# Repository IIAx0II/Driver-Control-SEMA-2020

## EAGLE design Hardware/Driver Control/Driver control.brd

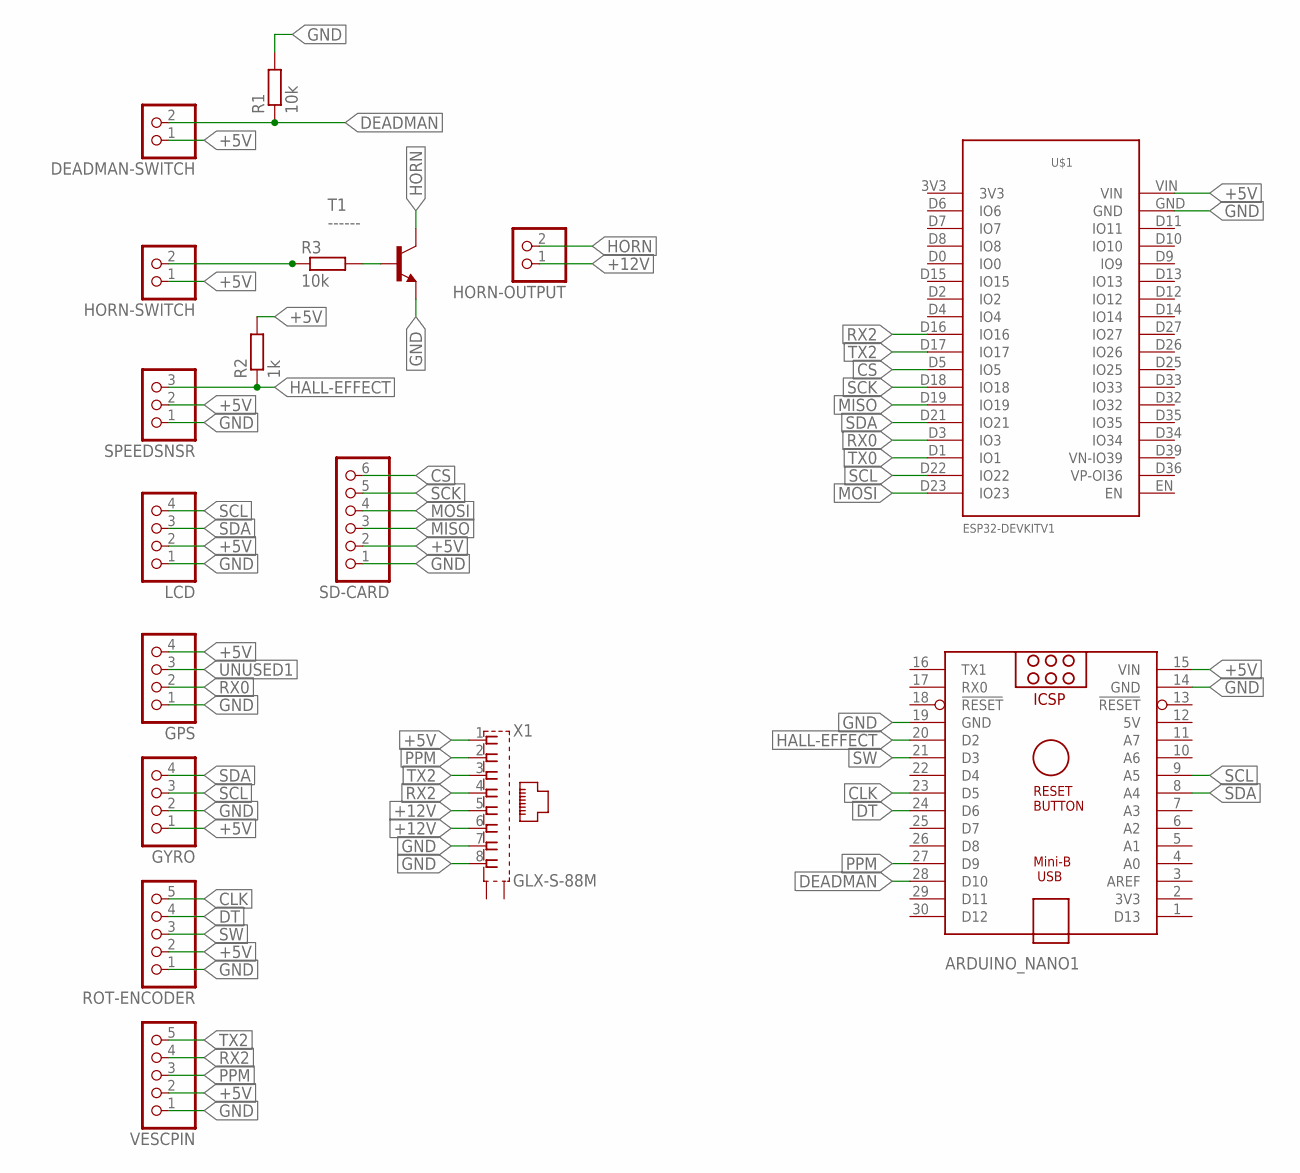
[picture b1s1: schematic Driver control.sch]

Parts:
ARDUINO_NANO1: ARDUINO_NANO
DEADMAN-SWITCH: PINHD-1X2; 1X02
GPS: PINHD-1X4; 1X04
GYRO: PINHD-1X4; 1X04
HORN-OUTPUT: PINHD-1X2; 1X02
HORN-SWITCH: PINHD-1X2; 1X02
LCD: PINHD-1X4; 1X04
R1, R3: 10k; 0204/7
R2: 1k; 0204/7
ROT-ENCODER: PINHD-1X5; 1X05
SD-CARD: PINHD-1X6; 1X06
SPEEDSNSR: PINHD-1X3; 1X03
T1: ------; TO5
U$1: ESP32DEVKITV1; ESP32-DEVKITV1
VESCPIN: PINHD-1X5; 1X05
X1: GLX-S-88M

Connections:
5V: ARDUINO_NANO1.12 (5V)
+5V: ARDUINO_NANO1.15 (VIN), DEADMAN-SWITCH.1, GPS.4, GYRO.1, HORN-SWITCH.1, LCD.2, R2.2, ROT-ENCODER.2, SD-CARD.2, SPEEDSNSR.2, U$1.VIN, VESCPIN.2, X1.1
+12V: HORN-OUTPUT.1, X1.5, X1.6
CLK: ARDUINO_NANO1.23 (D5), ROT-ENCODER.5
CS: SD-CARD.6, U$1.D5 (IO5)
DEADMAN: ARDUINO_NANO1.28 (D10), DEADMAN-SWITCH.2, R1.1
DT: ARDUINO_NANO1.24 (D6), ROT-ENCODER.4
GND: ARDUINO_NANO1.14 (GND), ARDUINO_NANO1.19 (GND), GPS.1, GYRO.2, LCD.1, R1.2, ROT-ENCODER.1, SD-CARD.1, SPEEDSNSR.1, T1.1 (E), U$1.GND, VESCPIN.1, X1.7, X1.8
HALL-EFFECT: ARDUINO_NANO1.20 (D2), R2.1, SPEEDSNSR.3
HORN: HORN-OUTPUT.2, T1.3 (C)
MISO: SD-CARD.3, U$1.D19 (IO19)
MOSI: SD-CARD.4, U$1.D23 (IO23)
unnamed: HORN-SWITCH.2, R3.1
unnamed: R3.2, T1.2 (B)
PPM: ARDUINO_NANO1.27 (D9), VESCPIN.3, X1.2
RX0: GPS.2, U$1.D3 (IO3)
RX2: U$1.D16 (IO16), VESCPIN.4, X1.4
SCK: SD-CARD.5, U$1.D18 (IO18)
SCL: ARDUINO_NANO1.9 (A5), GYRO.3, LCD.4, U$1.D22 (IO22)
SDA: ARDUINO_NANO1.8 (A4), GYRO.4, LCD.3, U$1.D21 (IO21)
SW: ARDUINO_NANO1.21 (D3), ROT-ENCODER.3
TX0: U$1.D1 (IO1)
TX2: U$1.D17 (IO17), VESCPIN.5, X1.3
UNUSED1: GPS.3

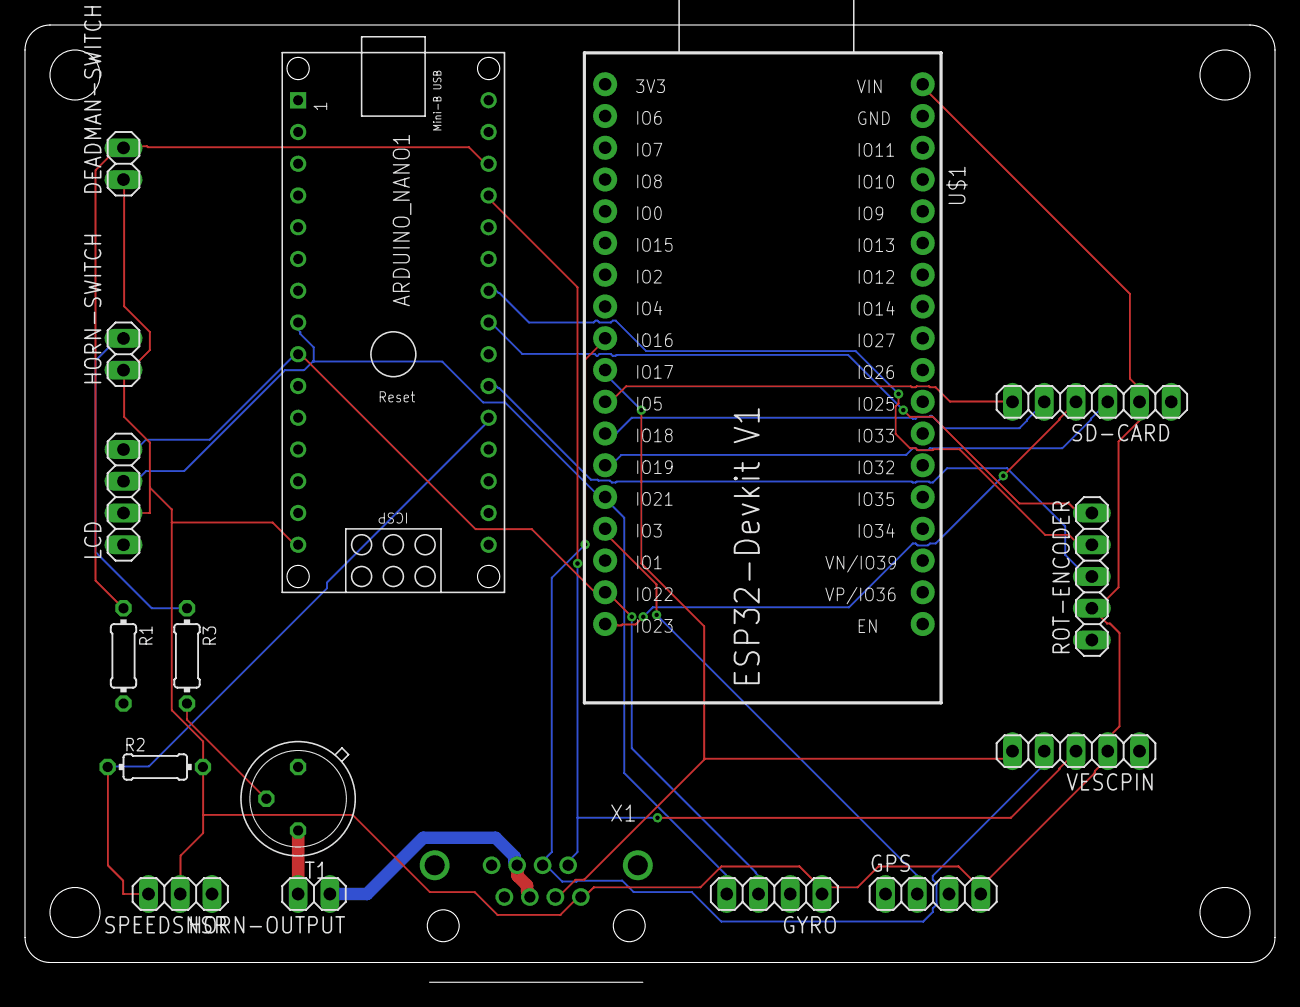
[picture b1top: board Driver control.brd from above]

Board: 2 copper layers, 100.0 x 76.6 mm, 17 parts (0 on the bottom side), 21 nets.

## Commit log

2020-02-16 Commit #1
2020-02-16 Added SEM to board
2020-02-16 Added more comments
